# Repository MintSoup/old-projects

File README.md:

# old-projects
An archive of my older projects

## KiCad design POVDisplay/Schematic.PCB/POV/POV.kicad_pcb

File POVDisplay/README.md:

# POV display
A rotating POV display using STM32.

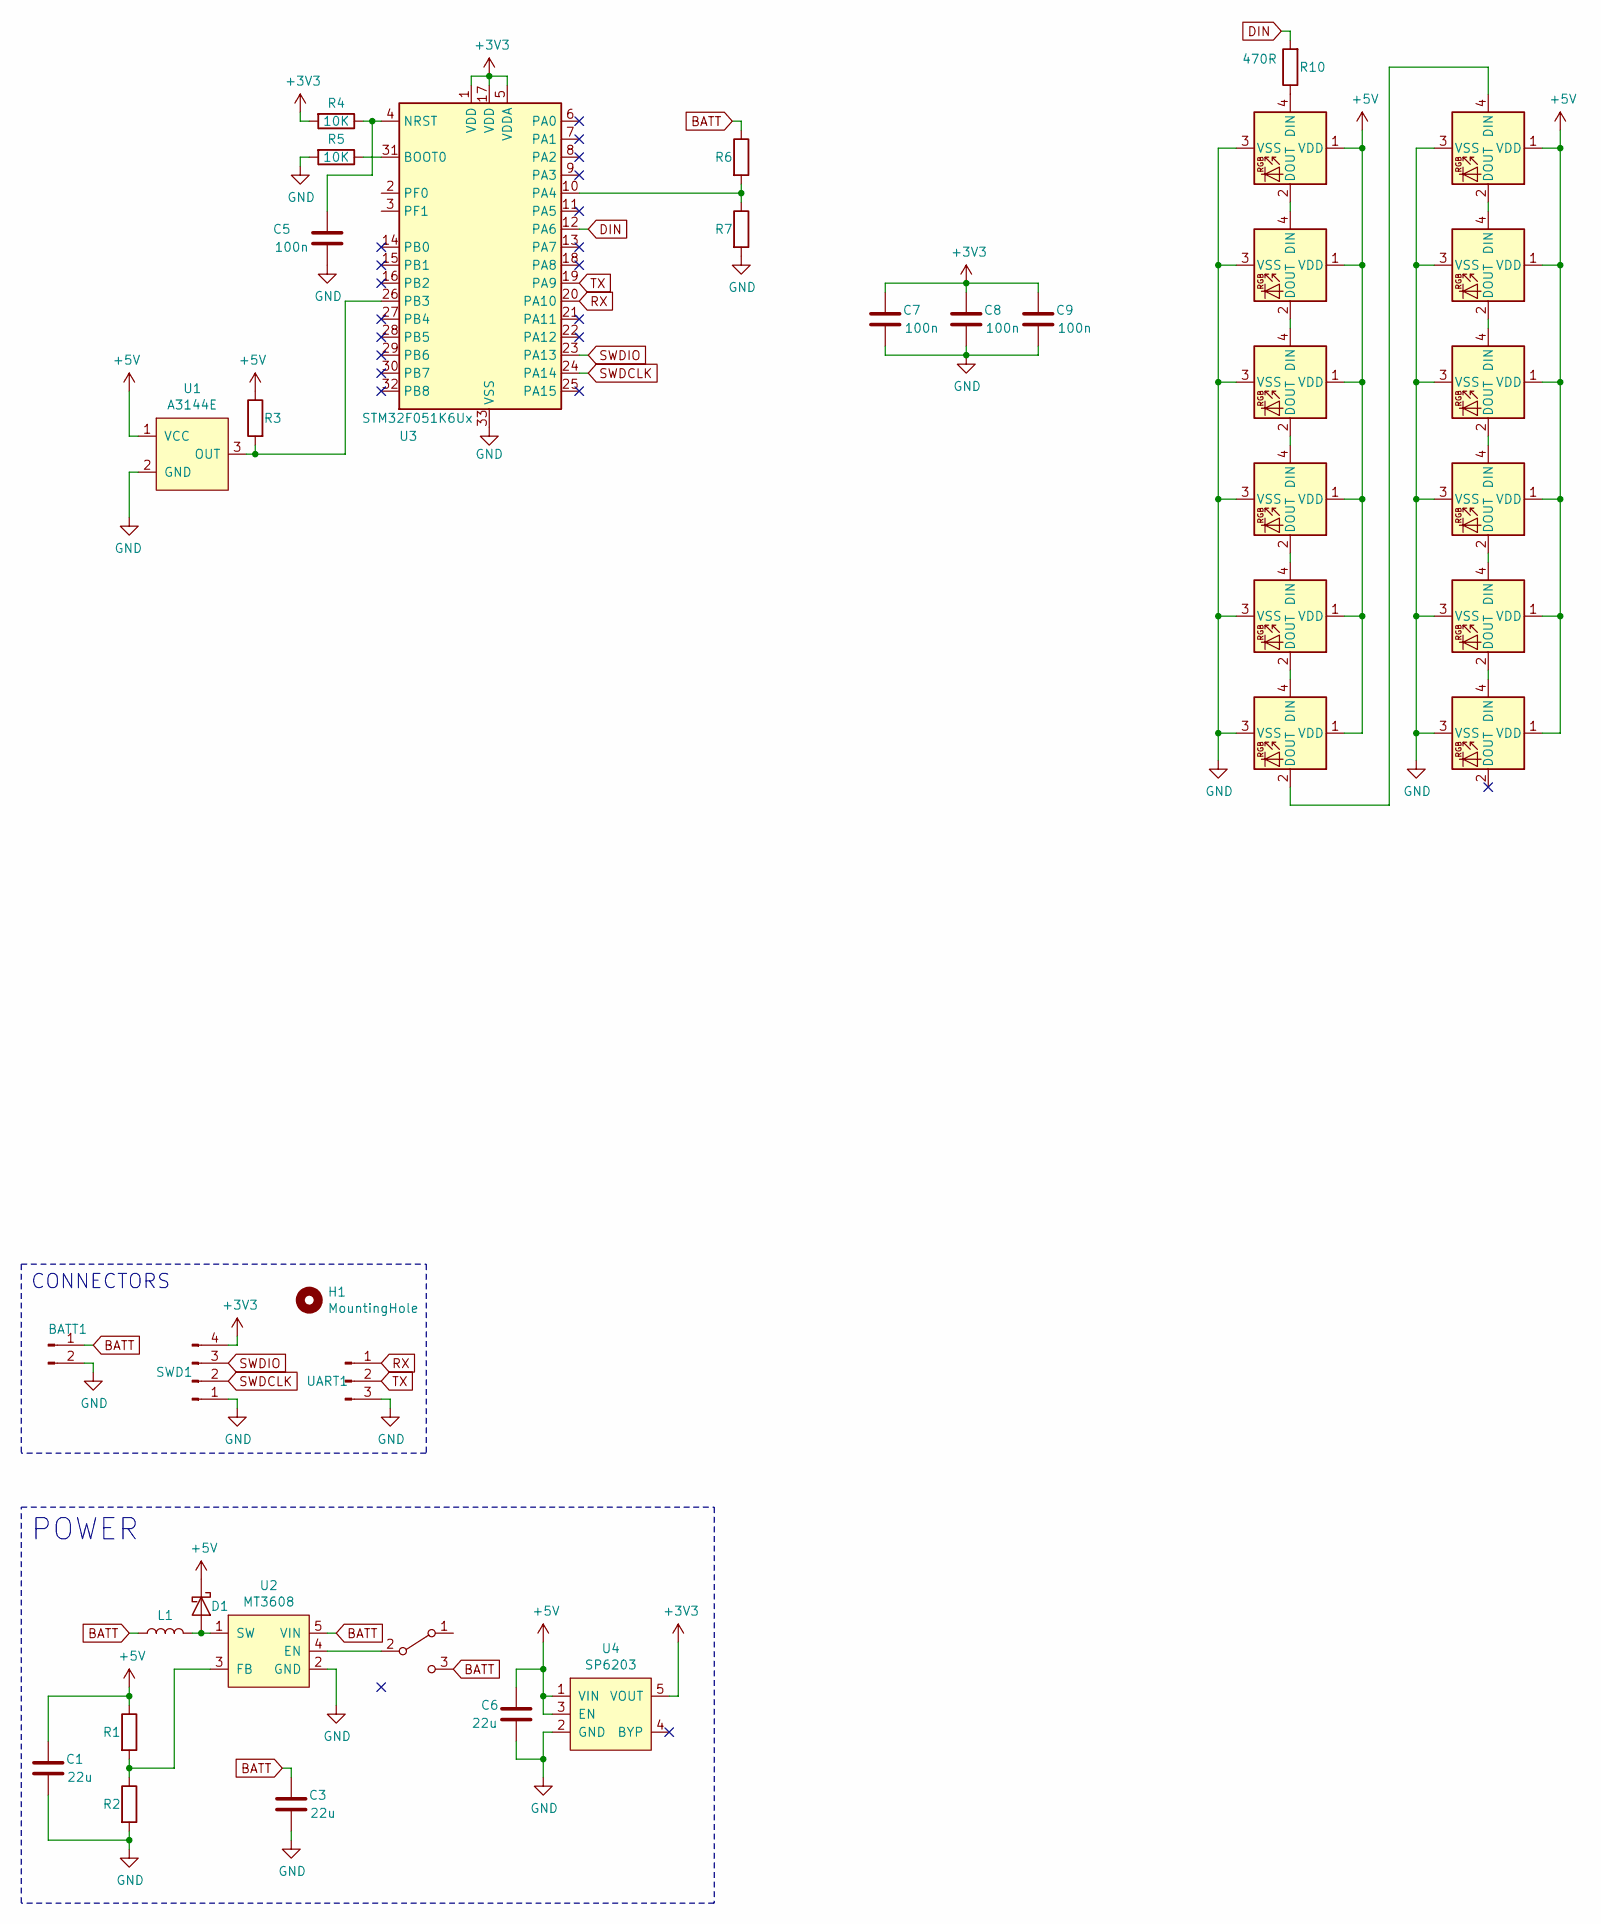
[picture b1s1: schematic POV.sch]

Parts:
BATT1: Conn_01x02_Male; PinHeader_1x02_P2.54mm_Vertical
C1, C3, C6: 22u; C_0603_1608Metric
C5, C7, C8, C9: 100n; C_0603_1608Metric
D1: D_Schottky; D_0603_1608Metric_Castellated
D4, D5, D6, D7, D8, D9, D10, D11, D12, D13, D14, D15: WS2812B; LED_WS2812B_PLCC4_5.0x5.0mm_P3.2mm
H1: MountingHole; MountingHole_2.5mm
L1: L; L_1210_3225Metric_Pad1.42x2.65mm_HandSolder
R1, R2, R6, R7: R_0603_1608Metric
R3: 1K; R_0603_1608Metric
R4, R5: 10K; R_0603_1608Metric
R10: 470R; R_0603_1608Metric
SW1: SW_SPDT; SW_SPDT_CK-JS102011SAQN
SWD1: Conn_01x04_Male; PinHeader_1x04_P2.54mm_Vertical
U1: A3144E; TO-92_Inline_Horizontal2
U2: MT3608; SOT-23-6_Handsoldering
U3: STM32F051K6Ux; QFN-32-1EP_5x5mm_P0.5mm_EP3.45x3.45mm
U4: SP6203; SOT-23-5_HandSoldering
UART1: Conn_01x03_Male; PinHeader_1x03_P2.54mm_Vertical

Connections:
+3V3: C7.1, C8.1, C9.1, R4.2, SWD1.4, U3.1 (VDD), U3.5 (VDDA), U3.17 (VDD), U4.5 (VOUT)
+5V: C1.1, C6.1, D1.1 (K), D4.1 (VDD), D5.1 (VDD), D6.1 (VDD), D7.1 (VDD), D8.1 (VDD), D9.1 (VDD), D10.1 (VDD), D11.1 (VDD), D12.1 (VDD), D13.1 (VDD), D14.1 (VDD), D15.1 (VDD), R1.1, R3.1, U1.1 (VCC), U4.1 (VIN), U4.3 (EN)
BATT: BATT1.1, C3.1, L1.2, R6.1, SW1.3 (C), U2.5 (VIN)
DIN: R10.2, U3.12 (PA6)
GND: BATT1.2, C1.2, C3.2, C5.2, C6.2, C7.2, C8.2, C9.2, D4.3 (VSS), D5.3 (VSS), D6.3 (VSS), D7.3 (VSS), D8.3 (VSS), D9.3 (VSS), D10.3 (VSS), D11.3 (VSS), D12.3 (VSS), D13.3 (VSS), D14.3 (VSS), D15.3 (VSS), R2.2, R5.2, R7.2, SWD1.1, U1.2 (GND), U2.2 (GND), U3.33 (VSS), U4.2 (GND), UART1.3
unnamed: C5.1, R4.1, U3.4 (NRST)
unnamed: D1.2 (A), L1.1, U2.1 (SW)
unnamed: D4.2 (DOUT), D5.4 (DIN)
unnamed: D4.4 (DIN), R10.1
unnamed: D5.2 (DOUT), D6.4 (DIN)
unnamed: D6.2 (DOUT), D7.4 (DIN)
unnamed: D7.2 (DOUT), D8.4 (DIN)
unnamed: D8.2 (DOUT), D9.4 (DIN)
unnamed: D10.2 (DOUT), D11.4 (DIN)
unnamed: D9.2 (DOUT), D10.4 (DIN)
unnamed: D11.2 (DOUT), D12.4 (DIN)
unnamed: D12.2 (DOUT), D13.4 (DIN)
unnamed: D13.2 (DOUT), D14.4 (DIN)
unnamed: D14.2 (DOUT), D15.4 (DIN)
unnamed: R1.2, R2.1, U2.3 (FB)
unnamed: R3.2, U1.3 (OUT), U3.26 (PB3)
unnamed: R5.1, U3.31 (BOOT0)
unnamed: R6.2, R7.1, U3.10 (PA4)
unnamed: SW1.2 (B), U2.4 (EN)
RX: U3.20 (PA10), UART1.1
SWDCLK: SWD1.2, U3.24 (PA14)
SWDIO: SWD1.3, U3.23 (PA13)
TX: U3.19 (PA9), UART1.2

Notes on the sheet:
POWER
CONNECTORS

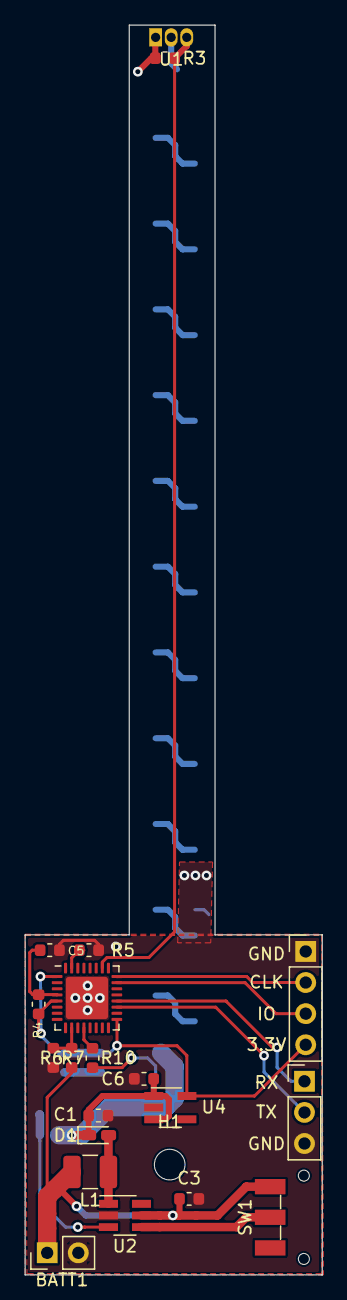
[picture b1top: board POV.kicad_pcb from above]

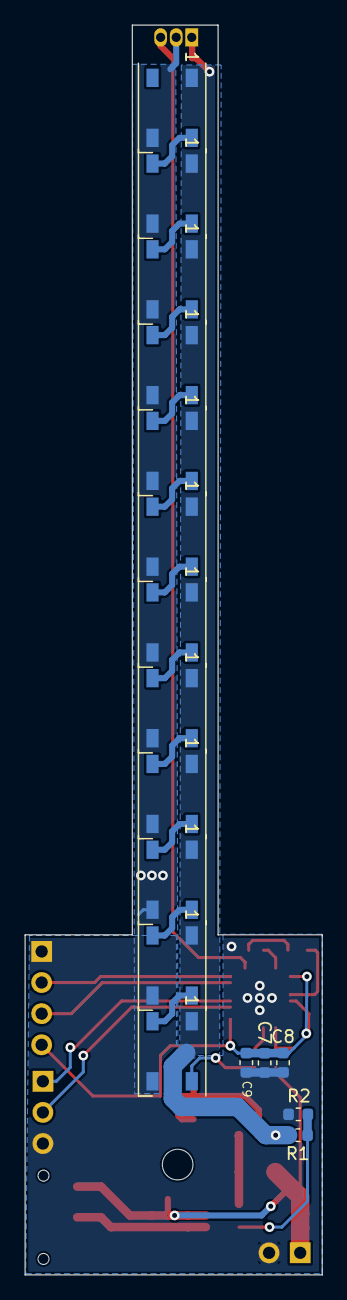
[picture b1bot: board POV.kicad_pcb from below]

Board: 4 copper layers, 24.2 x 102.0 mm, 38 parts (17 on the bottom side), 28 nets.

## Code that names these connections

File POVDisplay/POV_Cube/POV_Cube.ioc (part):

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Mcu.Name=STM32F051K6Ux
Mcu.Package=UFQFPN32
Mcu.UserName=STM32F051K6Ux
PA10.Mode=Asynchronous
PA10.Signal=USART1_RX
PA13.Mode=Serial_Wire
PA13.Signal=SYS_SWDIO
PA14.Mode=Serial_Wire
PA14.Signal=SYS_SWCLK
PA4.Mode=IN4
PA4.Signal=ADC_IN4
PA6.Signal=S_TIM3_CH1
PA9.Mode=Asynchronous
PA9.Signal=USART1_TX
PB3.Signal=S_TIM2_CH2
PF0-OSC_IN.Mode=HSE-External-Oscillator
PF0-OSC_IN.Signal=RCC_OSC_IN
PF1-OSC_OUT.Mode=HSE-External-Oscillator
PF1-OSC_OUT.Signal=RCC_OSC_OUT
board=custom

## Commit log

2020-09-28 Added projects
2020-09-28 Added READmes and did a little renaming
2020-09-28 Added some Fablab projects
2020-10-14 Added blender stuff
2022-02-23 Added f030 image
2022-02-23 Modify f030 readme
2022-02-23 Fix f030 readme
